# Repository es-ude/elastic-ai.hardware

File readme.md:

# Elastic Node Hardware Platform
This repo contains the hardware design files of our elastic node hardware for deploying deep learning architectures on embedded hardware.

## ENv6 - Elastic Node v6
Still in progress

## ENv5 - Elastic Node v5
The 5th generation of Elastic node is designed based on the 4th version, but with some improvements. The main improvements are:
- Using Cortex-M0 MCU instead of AVR 8-bit MCU, to gain more performance and lower power consumption.
- Using SPI as the communication interface between MCU and the FPGA to save more IO pins.
- Simplify the power supply circuit to reduce the space and improve reliability.
- Adding an energy meter chip to ease the energy measurement.
- Optimize the PCB layout to reduce the PCB size.

Before you start using the ENv5, please read the following documents accordingly:
- [ENv5 Test Version User Manual](v5/test_version/readme.md)
- [ENv5 Revision 1 User Manual](v5/revision_1/readme.md)

Troubleshooting
- When you notice the esp32 is not responding to the RP2040, you can apply the [pre-build firmware](v5/revision_1/prebuilds-firmware/test_esp_at.uf2) to test.
  - some descriptions about the behavior of the test are available [here](v5/revision_1/prebuilds-firmware/readme.md).

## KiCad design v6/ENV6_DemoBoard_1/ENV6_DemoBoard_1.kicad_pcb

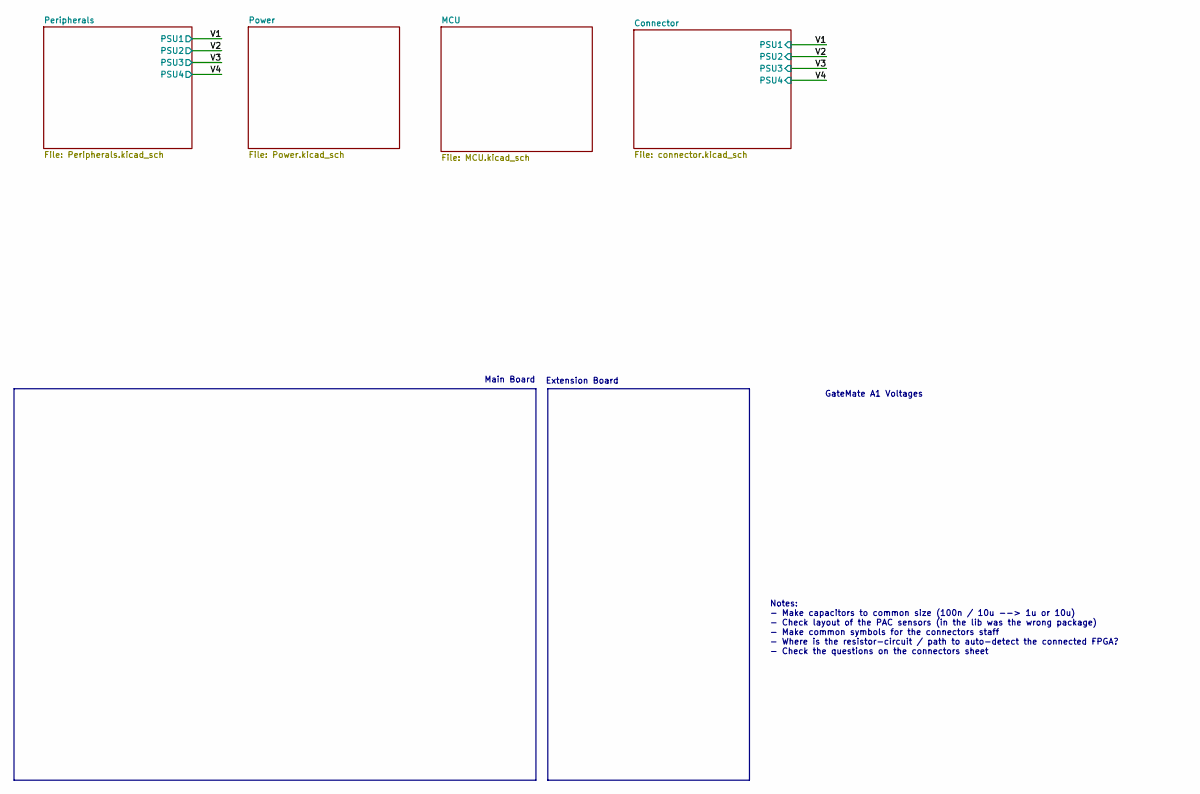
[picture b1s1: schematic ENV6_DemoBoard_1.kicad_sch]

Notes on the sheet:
Extension Board
Notes: - Make capacitors to common size (100n / 10u --> 1u or 10u) - Check layout of the PAC sensors (in the lib was the wrong package) - Make common symbols for the connectors staff - Where is the resistor-circuit / path to auto-detect the connected FPGA? - Check the questions on the connectors sh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
Main Board
GateMate A1 Voltages

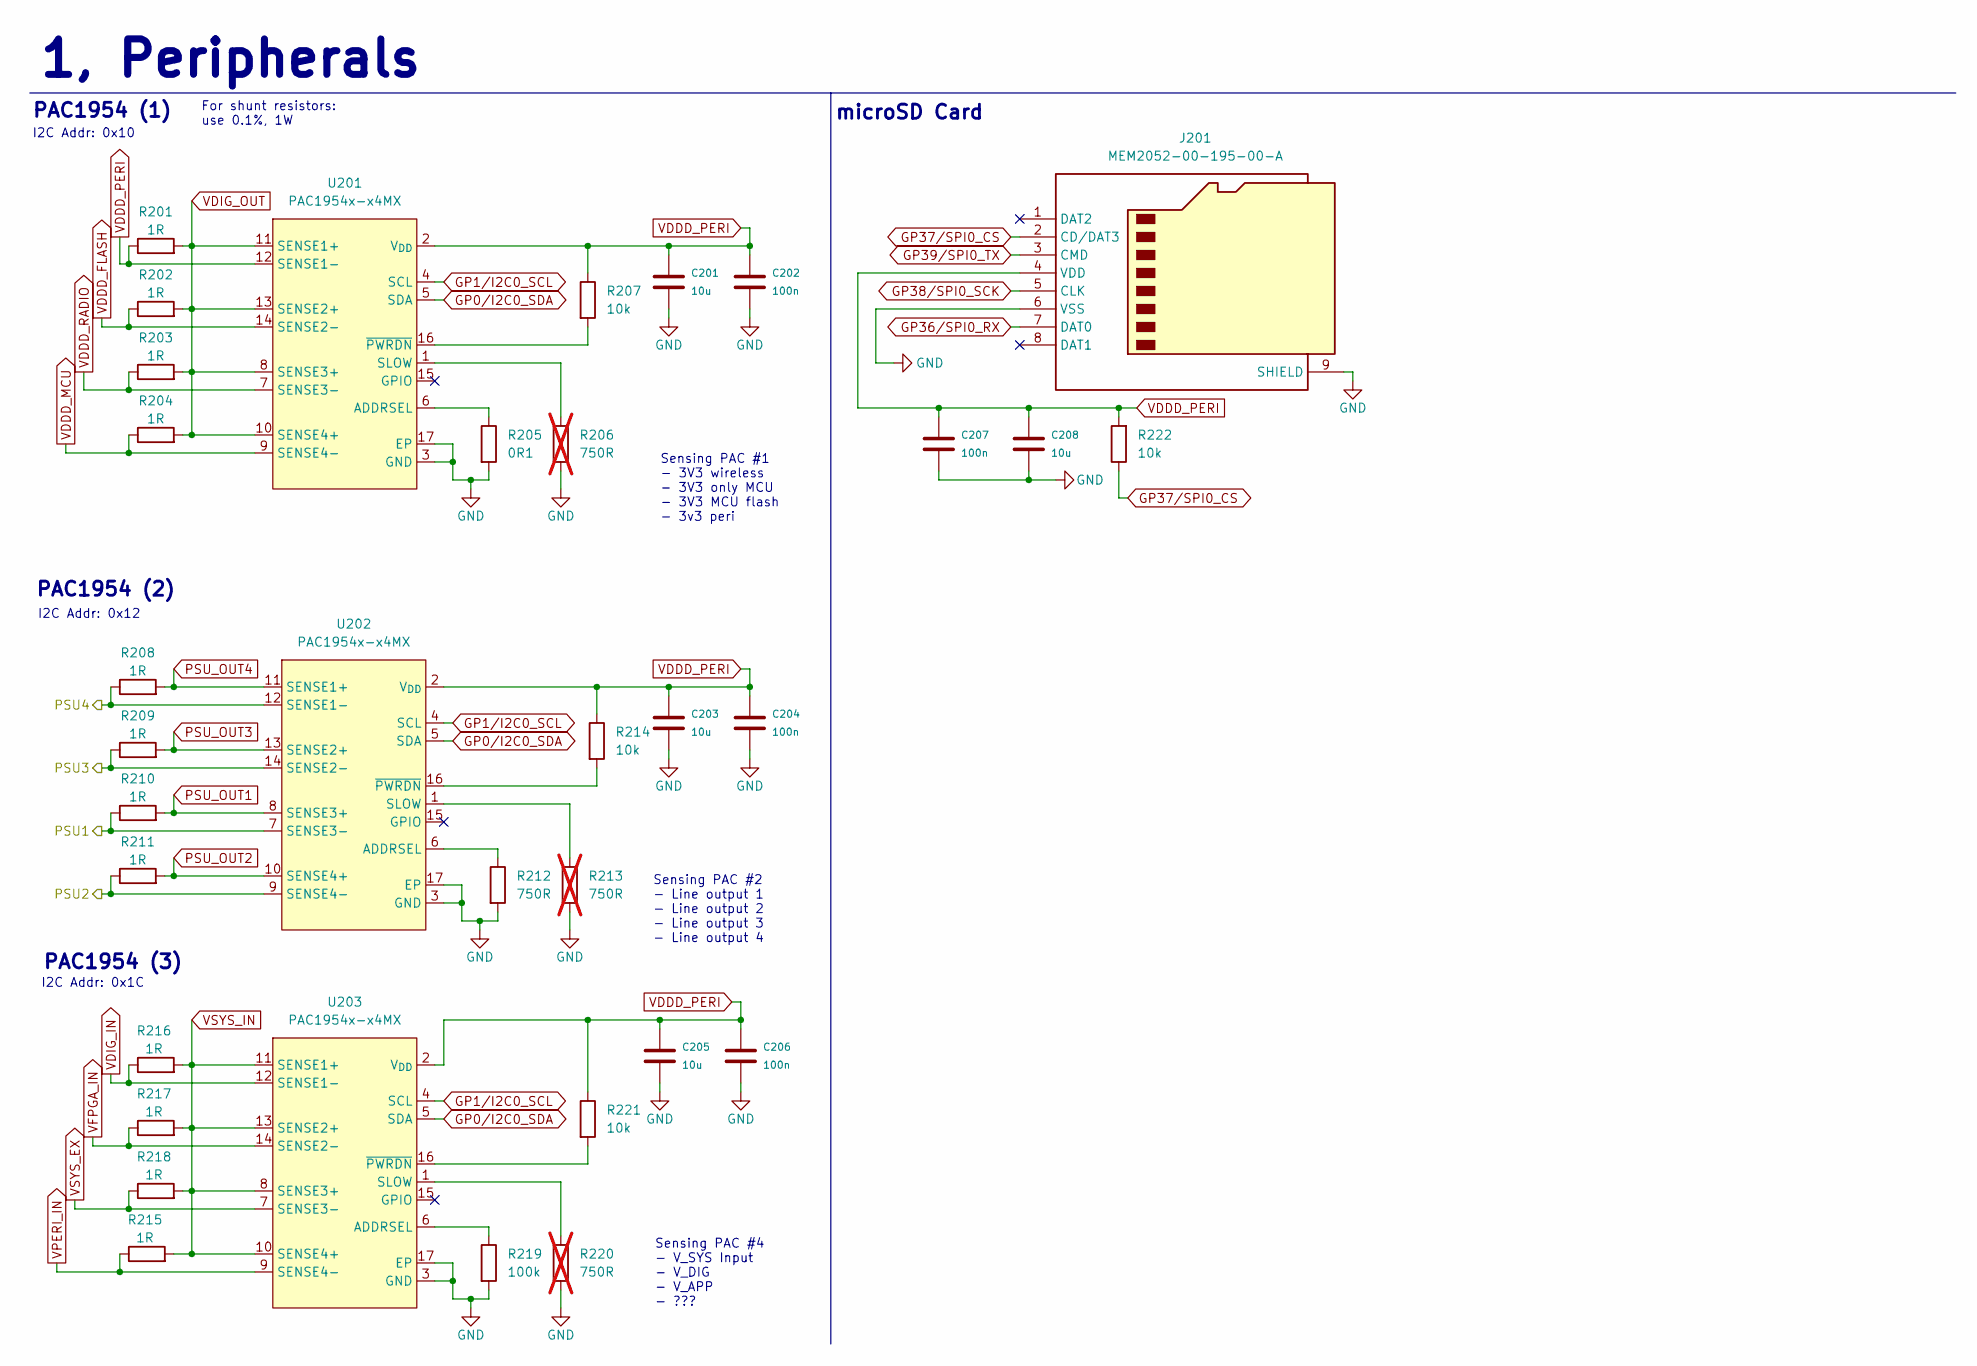
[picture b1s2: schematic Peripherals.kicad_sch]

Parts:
C201, C203, C205, C208: 10u; C_0402_1005Metric
C202, C204, C206, C207: 100n; C_0402_1005Metric
J201: MEM2052-00-195-00-A; MEM20520019500A; Mouser Part Number 640-MEM20520019500A
R201, R202, R203, R204, R208, R209, R210, R211, R215, R216, R217, R218: 1R; R_0603_1608Metric
R205: 0R1; R_0402_1005Metric
R206, R213, R220: 750R; R_0402_1005Metric; not fitted
R207, R214, R221, R222: 10k; R_0402_1005Metric
R212: 750R; R_0402_1005Metric
R219: 100k; R_0402_1005Metric
U201, U202, U203: PAC1954x-x4MX; VQFN-16-1EP_3x3mm_P0.5mm_EP1.1x1.1mm

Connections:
/V1: R210.1, U202.7 (SENSE3-); also elsewhere on the board
/V2: R211.1, U202.9 (SENSE4-); also elsewhere on the board
/V3: R209.1, U202.14 (SENSE2-); also elsewhere on the board
/V4: R208.1, U202.12 (SENSE1-); also elsewhere on the board
GND: C201.1, C202.1, C203.1, C204.1, C205.1, C206.1, C207.1, C208.1, J201.6 (VSS), J201.9 (SHIELD), J201.G1 (GND_1), J201.G2 (GND_2), J201.G3 (GND_3), J201.G4 (GND_4), R205.2, R206.2, R212.2, R213.2, R219.2, R220.2, U201.3 (GND), U201.17 (EP), U202.3 (GND), U202.17 (EP), U203.3 (GND), U203.17 (EP); also elsewhere on the board
GP0/I2C0_SDA: U201.5 (SDA), U202.5 (SDA), U203.5 (SDA); also elsewhere on the board
GP1/I2C0_SCL: U201.4 (SCL), U202.4 (SCL), U203.4 (SCL); also elsewhere on the board
GP36/SPI0_RX: J201.7 (DAT0); also elsewhere on the board
GP37/SPI0_CS: J201.2 (CD/DAT3), R222.1; also elsewhere on the board
GP38/SPI0_SCK: J201.5 (CLK); also elsewhere on the board
GP39/SPI0_TX: J201.3 (CMD); also elsewhere on the board
unnamed: R205.1, U201.6 (ADDRSEL)
unnamed: R206.1, U201.1 (SLOW)
unnamed: R207.2, U201.16 (~PWRDN)
unnamed: R212.1, U202.6 (ADDRSEL)
unnamed: R213.1, U202.1 (SLOW)
unnamed: R214.2, U202.16 (~PWRDN)
unnamed: R219.1, U203.6 (ADDRSEL)
unnamed: R220.1, U203.1 (SLOW)
unnamed: R221.2, U203.16 (~PWRDN)
PSU_OUT1: R210.2, U202.8 (SENSE3+); also elsewhere on the board
PSU_OUT2: R211.2, U202.10 (SENSE4+); also elsewhere on the board
PSU_OUT3: R209.2, U202.13 (SENSE2+); also elsewhere on the board
PSU_OUT4: R208.2, U202.11 (SENSE1+); also elsewhere on the board
VDDD_FLASH: R202.1, U201.14 (SENSE2-); also elsewhere on the board
VDDD_MCU: R204.1, U201.9 (SENSE4-); also elsewhere on the board
VDDD_PERI: C201.2, C202.2, C203.2, C204.2, C205.2, C206.2, C207.2, C208.2, J201.4 (VDD), R201.1, R207.1, R214.1, R221.1, R222.2, U201.2 (V_{DD}), U201.12 (SENSE1-), U202.2 (V_{DD}), U203.2 (V_{DD}); also elsewhere on the board
VDDD_RADIO: R203.1, U201.7 (SENSE3-); also elsewhere on the board
VDIG_IN: R216.1, U203.12 (SENSE1-); also elsewhere on the board
VDIG_OUT: R201.2, R202.2, R203.2, R204.2, U201.8 (SENSE3+), U201.10 (SENSE4+), U201.11 (SENSE1+), U201.13 (SENSE2+); also elsewhere on the board
VFPGA_IN: R217.1, U203.14 (SENSE2-); also elsewhere on the board
VPERI_IN: R215.1, U203.9 (SENSE4-); also elsewhere on the board
VSYS_EX: R218.1, U203.7 (SENSE3-); also elsewhere on the board
VSYS_IN: R215.2, R216.2, R217.2, R218.2, U203.8 (SENSE3+), U203.10 (SENSE4+), U203.11 (SENSE1+), U203.13 (SENSE2+); also elsewhere on the board

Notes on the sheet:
1, Peripherals
Sensing PAC #4 - V_SYS Input - V_DIG - V_APP - ???
PAC1954 (1)
microSD Card
Sensing PAC #1 - 3V3 wireless - 3V3 only MCU - 3V3 MCU flash - 3v3 peri
For shunt resistors: use 0.1%, 1W
I2C Addr: 0x1C
I2C Addr: 0x10
I2C Addr: 0x12
Sensing PAC #2 - Line output 1 - Line output 2 - Line output 3 - Line output 4
PAC1954 (2)
PAC1954 (3)

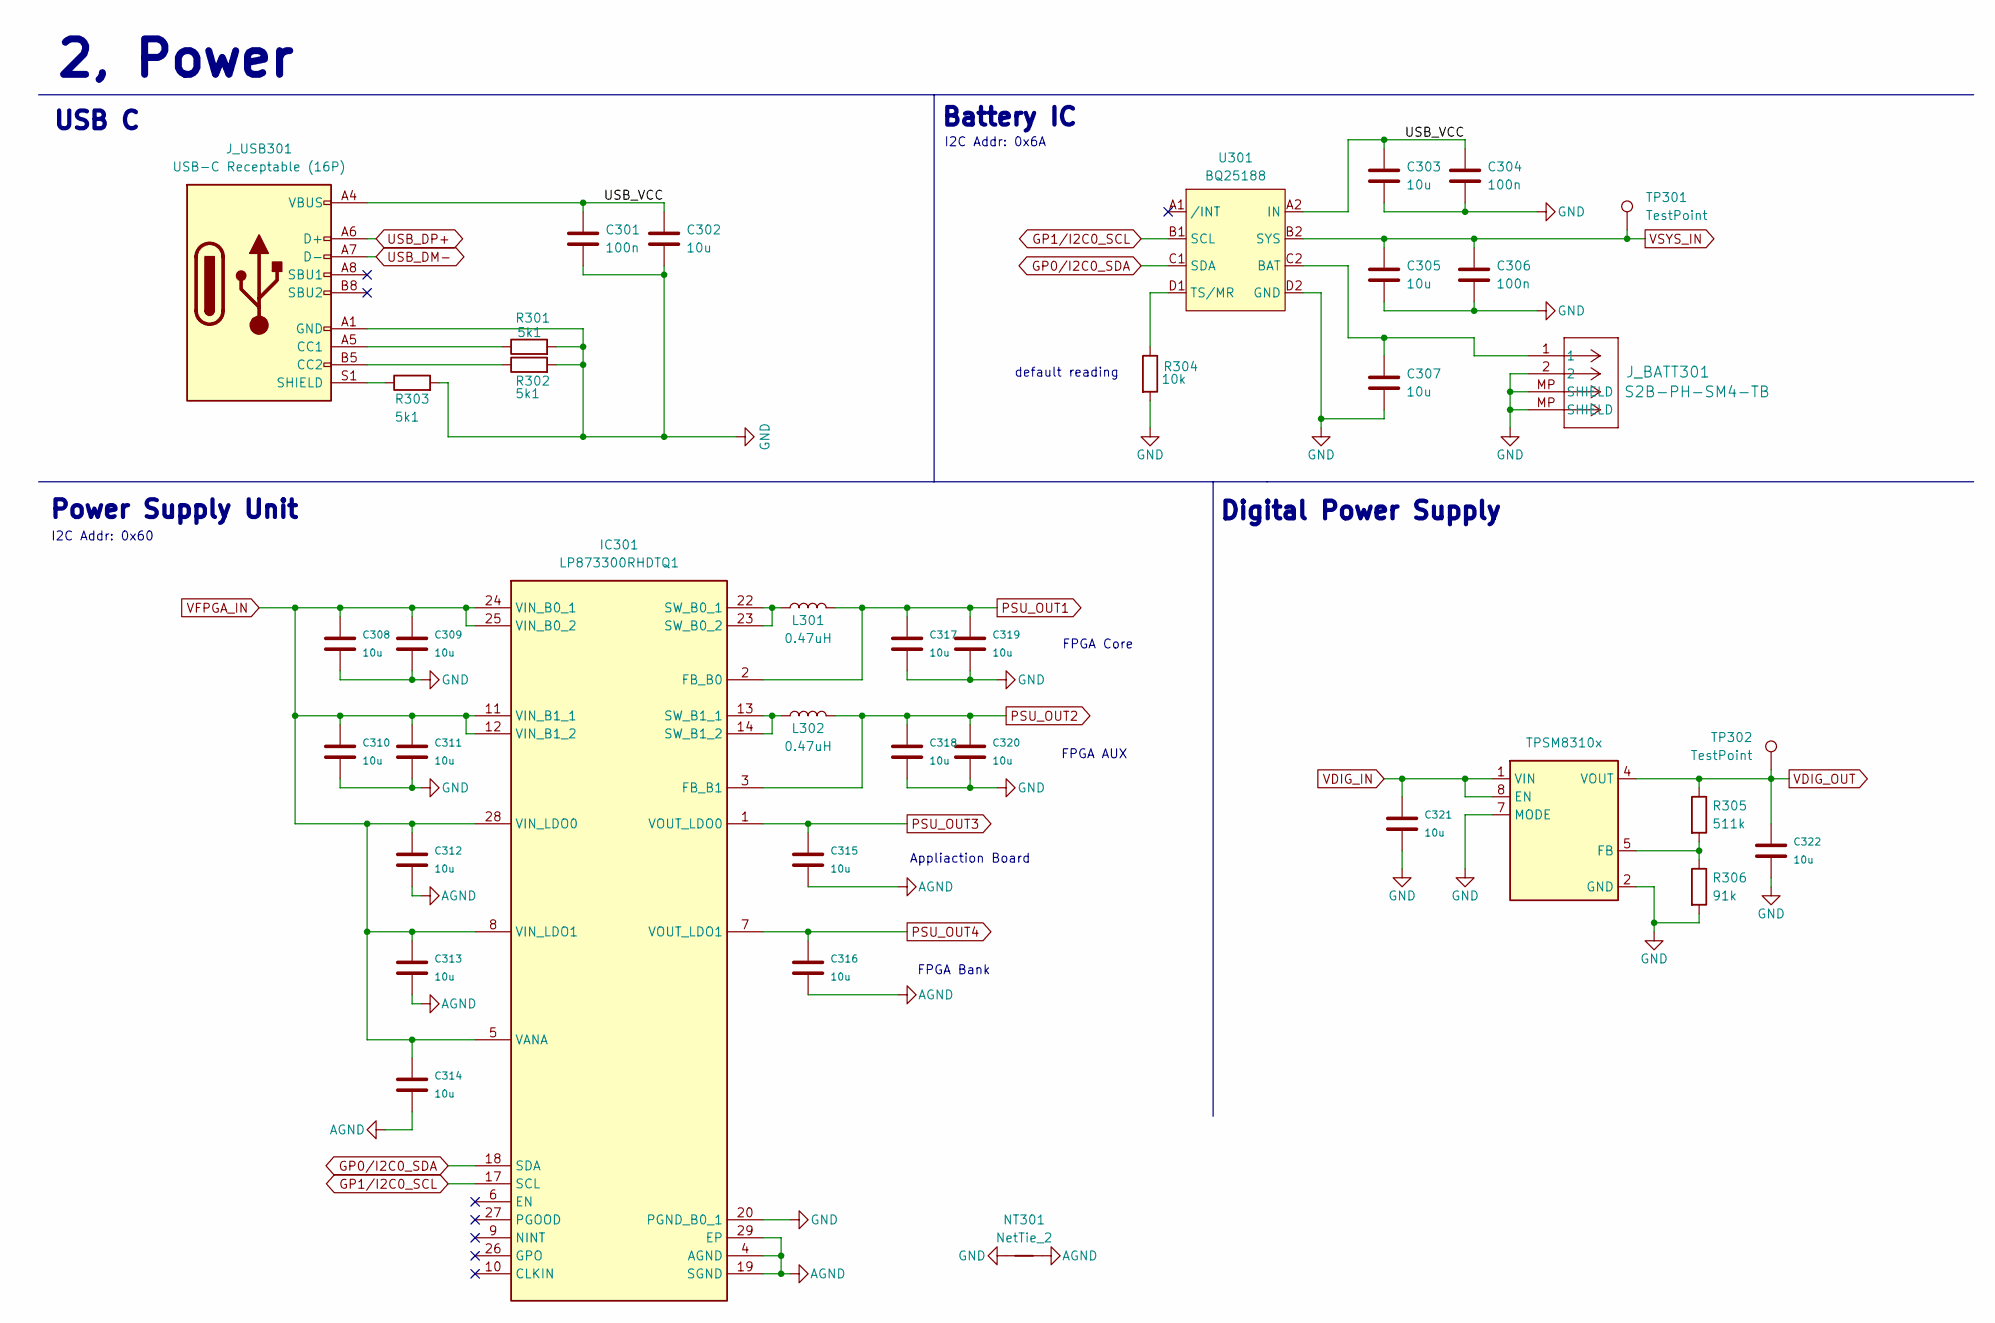
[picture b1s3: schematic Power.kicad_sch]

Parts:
C301, C304, C306: 100n; C_0402_1005Metric
C302, C303, C305, C307, C308, C309, C310, C311, C312, C313, C314, C315, C316, C317, C318, C319, C320, C321, C322: 10u; C_0402_1005Metric
IC301: LP873300RHDTQ1; QFN50P500X500X80-29N; Mouser Part Number 595-LP873300RHDTQ1
J_BATT301: S2B-PH-SM4-TB; JST_PH_S2B-PH-SM4-TB_1x02-1MP_P2.00mm_Horizontal
J_USB301: USB-C Receptable (16P); USB_C_Receptacle_16P
L301, L302: 0.47uH; L_1008_2520Metric
NT301: NetTie_2; NetTie-2_SMD_Pad0.5mm
R301, R302, R303: 5k1; R_0402_1005Metric
R304: 10k; R_0402_1005Metric
R305: 511k; R_0402_1005Metric
R306: 91k; R_0402_1005Metric
TP301, TP302: TestPoint; TestPoint_Pad_D1.0mm
U301: BQ25188; Texas_DSBGA-8_0.9x1.9mm_Layout2x4_P0.5mm
U302: TPSM8310x; MICROSIP8_SIU_TEX

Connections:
/Power/USB_VCC: C301.1, C302.1, C303.1, C304.1, J_USB301.A4 (VBUS), J_USB301.A9 (VBUS), J_USB301.B4 (VBUS), J_USB301.B9 (VBUS), U301.A2 (IN)
AGND: C312.1, C313.1, C314.1, C315.1, C316.1, IC301.4 (AGND), IC301.19 (SGND), IC301.29 (EP), NT301.2
GND: C301.2, C302.2, C303.2, C304.2, C305.2, C306.2, C307.2, C308.1, C309.1, C310.1, C311.1, C317.1, C318.1, C319.1, C320.1, C321.1, C322.1, IC301.15 (PGND_B1_1), IC301.16 (PGND_B1_2), IC301.20 (PGND_B0_1), IC301.21 (PGND_B0_2), J_BATT301.2, J_BATT301.MP (SHIELD), J_USB301.A1 (GND), J_USB301.A12 (GND), J_USB301.B1 (GND), J_USB301.B12 (GND), NT301.1, R301.2, R302.2, R303.2, R304.2, R306.2, U301.D2 (GND), U302.2 (GND), U302.3 (GND), U302.6 (GND), U302.7 (MODE); also elsewhere on the board
GP0/I2C0_SDA: IC301.18 (SDA), U301.C1 (SDA); also elsewhere on the board
GP1/I2C0_SCL: IC301.17 (SCL), U301.B1 (SCL); also elsewhere on the board
unnamed: IC301.22 (SW_B0_1), IC301.23 (SW_B0_2), L301.1
unnamed: IC301.13 (SW_B1_1), IC301.14 (SW_B1_2), L302.1
unnamed: J_USB301.A5 (CC1), R301.1
unnamed: J_USB301.B5 (CC2), R302.1
unnamed: J_USB301.S1 (SHIELD), R303.1
unnamed: C307.1, J_BATT301.1, U301.C2 (BAT)
unnamed: R304.1, U301.D1 (TS/MR)
unnamed: R305.2, R306.1, U302.5 (FB)
PSU_OUT1: C317.2, C319.2, IC301.2 (FB_B0), L301.2; also elsewhere on the board
PSU_OUT2: C318.2, C320.2, IC301.3 (FB_B1), L302.2; also elsewhere on the board
PSU_OUT3: C315.2, IC301.1 (VOUT_LDO0); also elsewhere on the board
PSU_OUT4: C316.2, IC301.7 (VOUT_LDO1); also elsewhere on the board
USB_DM-: J_USB301.A7 (D-), J_USB301.B7 (D-); also elsewhere on the board
USB_DP+: J_USB301.A6 (D+), J_USB301.B6 (D+); also elsewhere on the board
VDIG_IN: C321.2, U302.1 (VIN), U302.8 (EN); also elsewhere on the board
VDIG_OUT: C322.2, R305.1, TP302.1 (1_1), U302.4 (VOUT); also elsewhere on the board
VFPGA_IN: C308.2, C309.2, C310.2, C311.2, C312.2, C313.2, C314.2, IC301.5 (VANA), IC301.8 (VIN_LDO1), IC301.11 (VIN_B1_1), IC301.12 (VIN_B1_2), IC301.24 (VIN_B0_1), IC301.25 (VIN_B0_2), IC301.28 (VIN_LDO0); also elsewhere on the board
VSYS_IN: C305.1, C306.1, TP301.1 (1_1), U301.B2 (SYS); also elsewhere on the board

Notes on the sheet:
Battery IC
FPGA Bank
I2C Addr: 0x6A
default reading
USB C
2, Power
FPGA Core
Power Supply Unit
FPGA AUX
I2C Addr: 0x60
Digital Power Supply
Appliaction Board

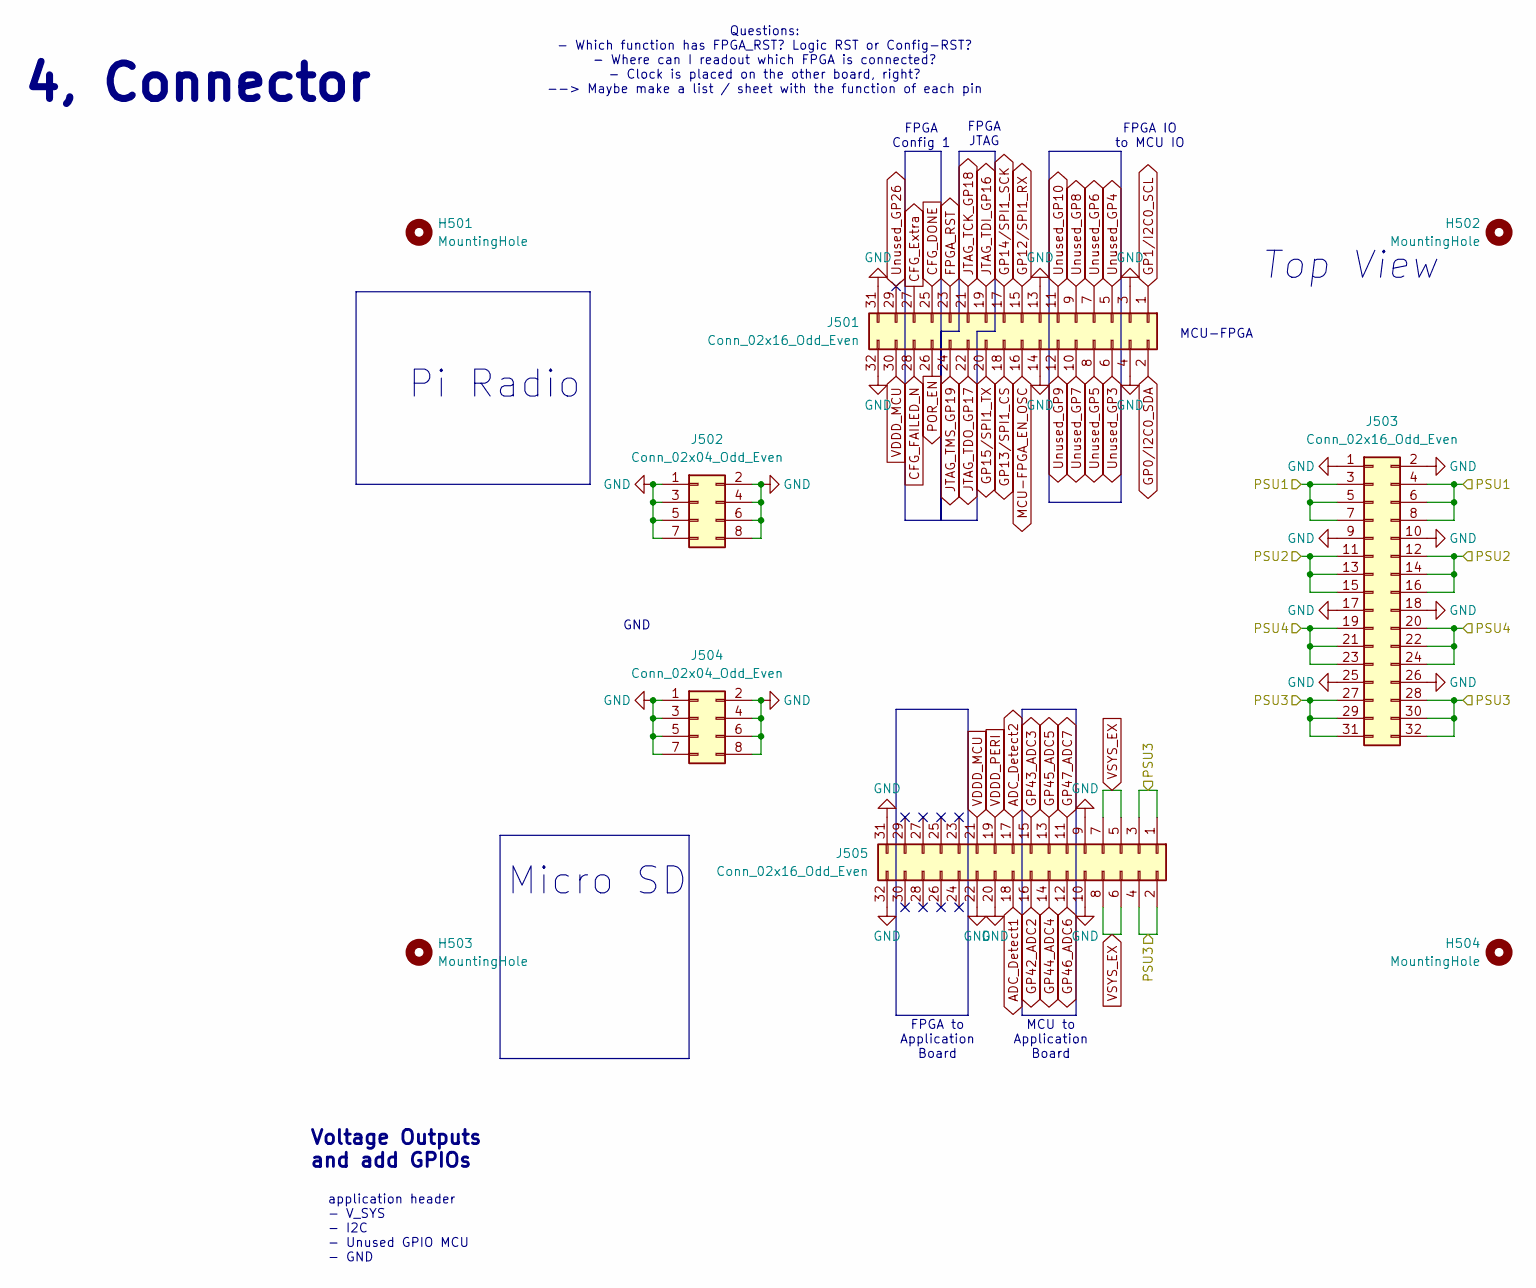
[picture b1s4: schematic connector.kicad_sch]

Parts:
H501, H502, H503, H504: MountingHole; MountingHole_2.5mm
J501, J503, J505: Conn_02x16_Odd_Even; PinHeader_2x16_P2.00mm_Vertical
J502, J504: Conn_02x04_Odd_Even; PinHeader_2x04_P2.00mm_Vertical

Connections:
/V1: J503.3, J503.4, J503.5, J503.6, J503.7, J503.8; also elsewhere on the board
/V2: J503.11, J503.12, J503.13, J503.14, J503.15, J503.16; also elsewhere on the board
/V3: J503.27, J503.28, J503.29, J503.30, J503.31, J503.32, J505.1, J505.2, J505.3, J505.4; also elsewhere on the board
/V4: J503.19, J503.20, J503.21, J503.22, J503.23, J503.24; also elsewhere on the board
ADC_Detect1: J505.18; also elsewhere on the board
ADC_Detect2: J505.17; also elsewhere on the board
CFG_DONE: J501.25; also elsewhere on the board
CFG_Extra: J501.27; also elsewhere on the board
CFG_FAILED_N: J501.28; also elsewhere on the board
FPGA_RST: J501.23; also elsewhere on the board
GND: J501.3, J501.4, J501.13, J501.14, J501.31, J501.32, J502.1, J502.2, J502.3, J502.4, J502.5, J502.6, J502.7, J502.8, J503.1, J503.2, J503.9, J503.10, J503.17, J503.18, J503.25, J503.26, J504.1, J504.2, J504.3, J504.4, J504.5, J504.6, J504.7, J504.8, J505.9, J505.10, J505.20, J505.22, J505.31, J505.32; also elsewhere on the board
GP0/I2C0_SDA: J501.2; also elsewhere on the board
GP1/I2C0_SCL: J501.1; also elsewhere on the board
GP12/SPI1_RX: J501.15; also elsewhere on the board
GP13/SPI1_CS: J501.18; also elsewhere on the board
GP14/SPI1_SCK: J501.17; also elsewhere on the board
GP15/SPI1_TX: J501.20; also elsewhere on the board
GP42_ADC2: J505.16; also elsewhere on the board
GP43_ADC3: J505.15; also elsewhere on the board
GP44_ADC4: J505.14; also elsewhere on the board
GP45_ADC5: J505.13; also elsewhere on the board
GP46_ADC6: J505.12; also elsewhere on the board
GP47_ADC7: J505.11; also elsewhere on the board
JTAG_TCK_GP18: J501.21; also elsewhere on the board
JTAG_TDI_GP16: J501.19; also elsewhere on the board
JTAG_TDO_GP17: J501.22; also elsewhere on the board
JTAG_TMS_GP19: J501.24; also elsewhere on the board
MCU-FPGA_EN_OSC: J501.16; also elsewhere on the board
POR_EN: J501.26; also elsewhere on the board
Unused_GP3: J501.6; also elsewhere on the board
Unused_GP4: J501.5; also elsewhere on the board
Unused_GP5: J501.8; also elsewhere on the board
Unused_GP6: J501.7; also elsewhere on the board
Unused_GP7: J501.10; also elsewhere on the board
Unused_GP8: J501.9; also elsewhere on the board
Unused_GP9: J501.12; also elsewhere on the board
Unused_GP10: J501.11; also elsewhere on the board
Unused_GP26: J501.29; also elsewhere on the board
VDDD_MCU: J501.30, J505.21; also elsewhere on the board
VDDD_PERI: J505.19; also elsewhere on the board
VSYS_EX: J505.5, J505.6, J505.7, J505.8; also elsewhere on the board

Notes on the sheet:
MCU-FPGA
FPGA IO to MCU IO
Questions: - Which function has FPGA_RST? Logic RST or Config-RST? - Where can I readout which FPGA is connected? - Clock is placed on the other board, right? --> Maybe make a list / sheet with the function of each pin
FPGA to Application Board
Top View
MCU to Application Board
4, Connector
GND
FPGA JTAG
Micro SD
Pi Radio
application header - V_SYS - I2C - Unused GPIO MCU - GND
Voltage Outputs and add GPIOs
FPGA Config 1

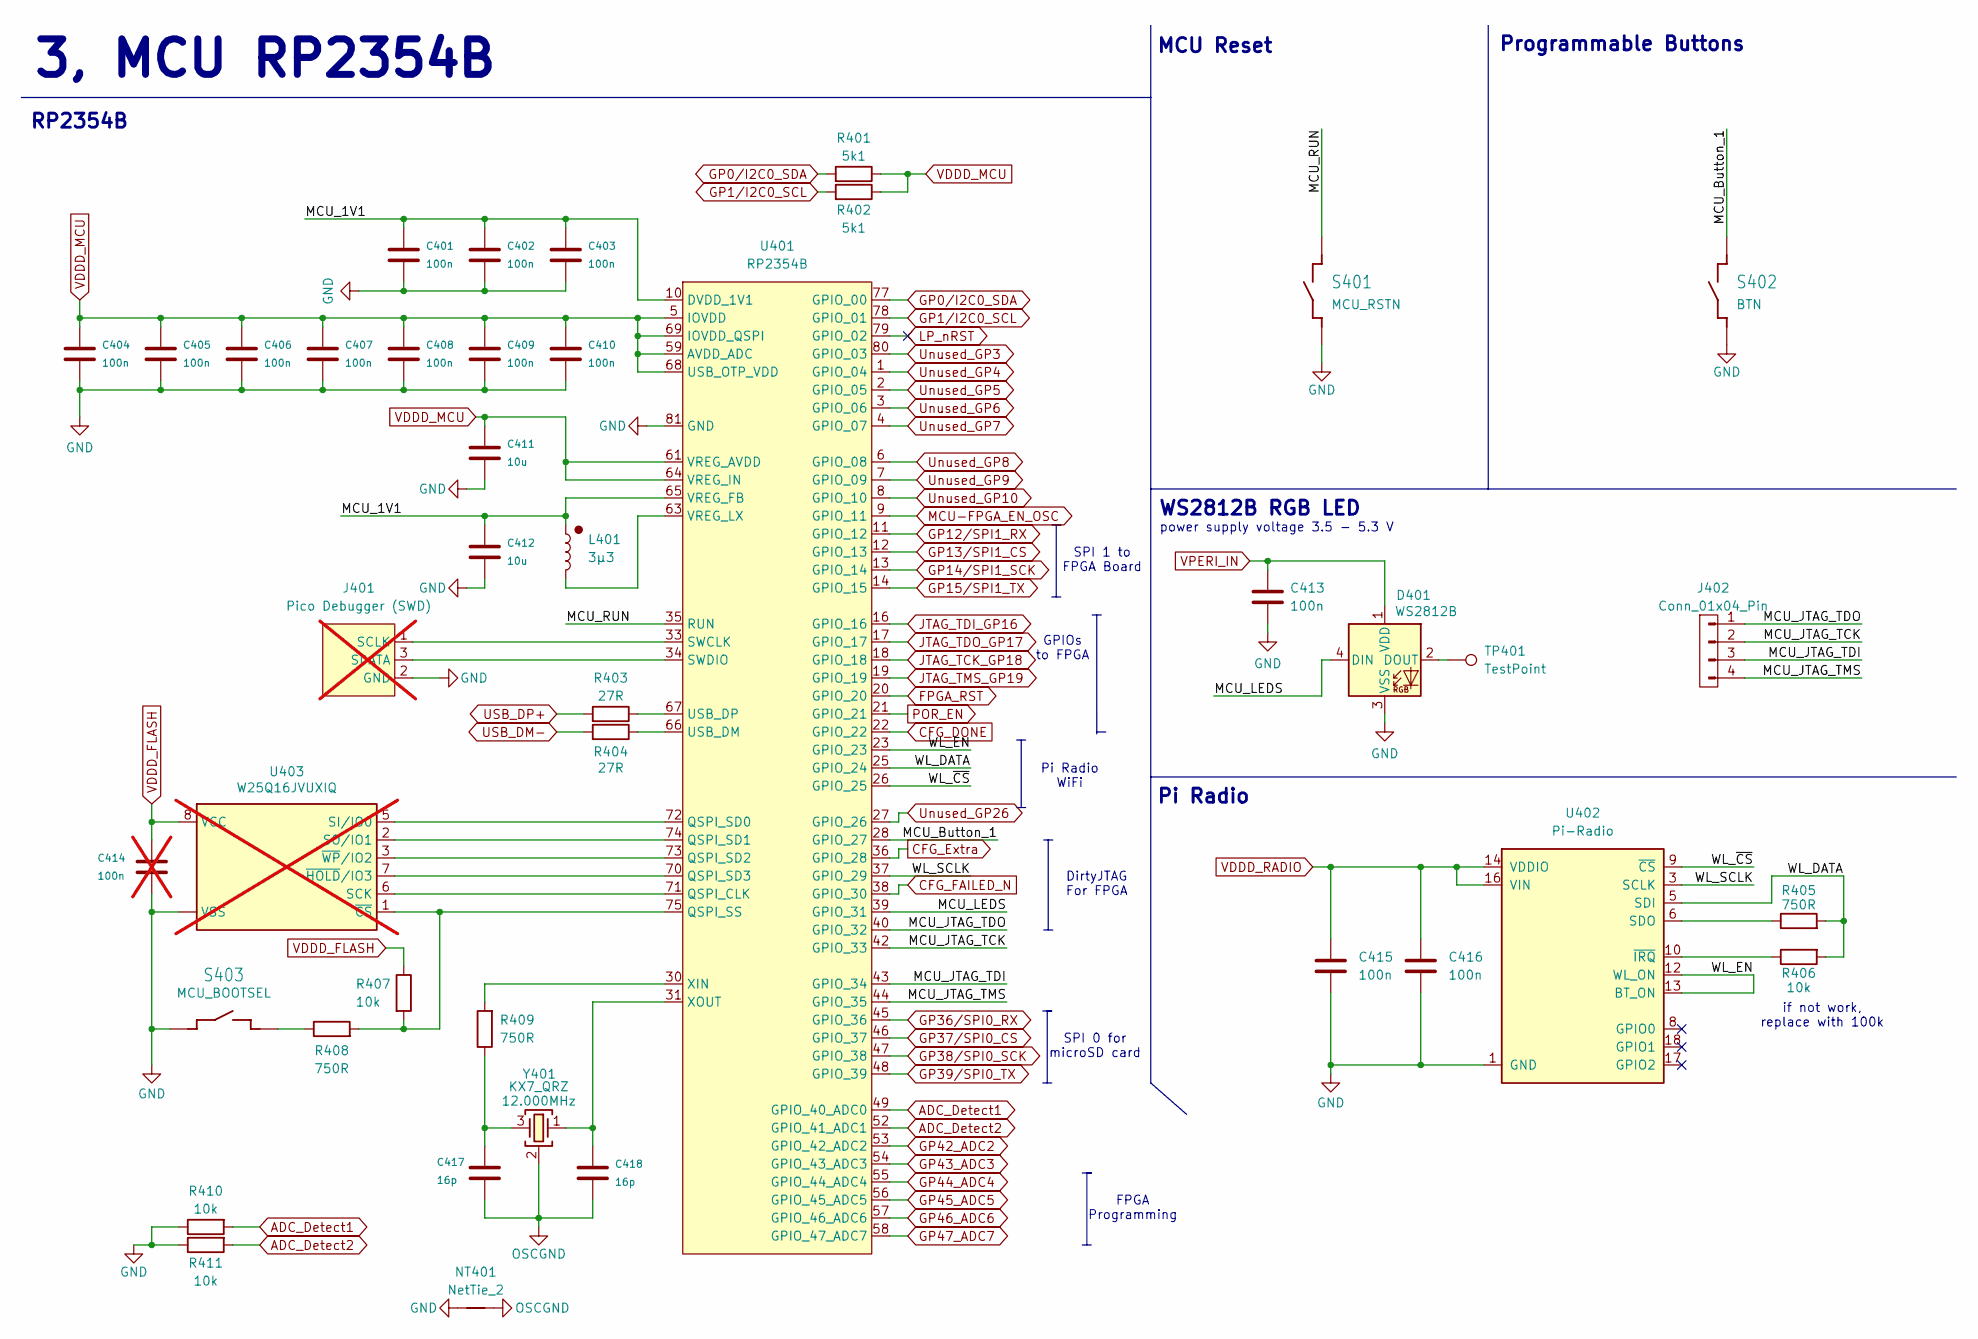
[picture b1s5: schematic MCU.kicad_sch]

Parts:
C401, C402, C403, C404, C405, C406, C407, C408, C409, C410, C413, C415, C416: 100n; C_0402_1005Metric
C411, C412: 10u; C_0402_1005Metric
C414: 100n; C_0402_1005Metric; not fitted
C417, C418: 16p; C_0402_1005Metric
D401: WS2812B; LED_WS2812B_PLCC4_5.0x5.0mm_P3.2mm
J401: Pico Debugger (SWD); PinHeader_1x03_P2.00mm_Vertical; not fitted
J402: Conn_01x04_Pin; PinSocket_1x04_P2.00mm_Vertical
L401: 3µ3; L_0805_2012_metric_Alligned_HandSolder
NT401: NetTie_2; NetTie-2_SMD_Pad0.5mm
R401, R402: 5k1; R_0402_1005Metric
R403, R404: 27R; R_0402_1005Metric
R405, R408, R409: 750R; R_0402_1005Metric
R406, R407, R410, R411: 10k; R_0402_1005Metric
S401: MCU_RSTN; TACTILE-SWITCH
S402: BTN; TACTILE-SWITCH
S403: MCU_BOOTSEL; TACTILE-SWITCH
TP401: TestPoint; TestPoint_Pad_D1.0mm
U401: RP2354B; QFN-80_EP_10x10_Pitch0.4mm
U402: Pi-Radio; RPi-Radio-Module
U403: W25Q16JVUXIQ; USON-8-1EP_3x2mm_P0.5mm_EP0.2x1.6mm; not fitted
Y401: KX7_QRZ; KX-7; MPN ABM8G-25.000MHZ-18-D2Y-T3

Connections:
/MCU/MCU_1V1: C401.2, C402.2, C403.2, C412.2, L401.1, U401.10 (DVDD_1V1), U401.32 (DVDD_1V1), U401.51 (DVDD_1V1), U401.65 (VREG_FB)
/MCU/MCU_Button_1: S402.3 (2), S402.4 (2), U401.28 (GPIO_27)
/MCU/MCU_JTAG_TCK: J402.2, U401.42 (GPIO_33)
/MCU/MCU_JTAG_TDI: J402.3, U401.43 (GPIO_34)
/MCU/MCU_JTAG_TDO: J402.1, U401.40 (GPIO_32)
/MCU/MCU_JTAG_TMS: J402.4, U401.44 (GPIO_35)
/MCU/MCU_LEDS: D401.4 (DIN), U401.39 (GPIO_31)
/MCU/MCU_RUN: S401.3 (2), S401.4 (2), U401.35 (RUN)
/MCU/WL_DATA: R405.2, R406.2, U401.25 (GPIO_24), U402.5 (SDI)
/MCU/WL_EN: U401.23 (GPIO_23), U402.12 (WL_ON), U402.13 (BT_ON)
/MCU/WL_SCLK: U401.37 (GPIO_29), U402.3 (SCLK)
/MCU/WL_~CS: U401.26 (GPIO_25), U402.9 (~CS)
ADC_Detect1: R410.2, U401.49 (GPIO_40_ADC0); also elsewhere on the board
ADC_Detect2: R411.2, U401.52 (GPIO_41_ADC1); also elsewhere on the board
CFG_DONE: U401.22 (GPIO_22); also elsewhere on the board
CFG_Extra: U401.36 (GPIO_28); also elsewhere on the board
CFG_FAILED_N: U401.38 (GPIO_30); also elsewhere on the board
FPGA_RST: U401.20 (GPIO_20); also elsewhere on the board
GND: C401.1, C402.1, C403.1, C404.1, C405.1, C406.1, C407.1, C408.1, C409.1, C410.1, C411.1, C412.1, C413.2, C414.2, C415.2, C416.2, D401.3 (VSS), J401.2 (GND), NT401.1, R410.1, R411.1, S401.1, S401.2 (1), S402.1, S402.2 (1), S403.1, S403.2 (1), U401.62 (GND), U401.81 (GND), U402.1 (GND), U402.4 (GND), U402.7 (GND), U402.11 (GND), U402.15 (GND), U402.21 (GND), U403.4 (VSS), U403.9 (VSS); also elsewhere on the board
GP0/I2C0_SDA: R401.2, U401.77 (GPIO_00); also elsewhere on the board
GP1/I2C0_SCL: R402.2, U401.78 (GPIO_01); also elsewhere on the board
GP12/SPI1_RX: U401.11 (GPIO_12); also elsewhere on the board
GP13/SPI1_CS: U401.12 (GPIO_13); also elsewhere on the board
GP14/SPI1_SCK: U401.13 (GPIO_14); also elsewhere on the board
GP15/SPI1_TX: U401.14 (GPIO_15); also elsewhere on the board
GP36/SPI0_RX: U401.45 (GPIO_36); also elsewhere on the board
GP37/SPI0_CS: U401.46 (GPIO_37); also elsewhere on the board
GP38/SPI0_SCK: U401.47 (GPIO_38); also elsewhere on the board
GP39/SPI0_TX: U401.48 (GPIO_39); also elsewhere on the board
GP42_ADC2: U401.53 (GPIO_42_ADC2); also elsewhere on the board
GP43_ADC3: U401.54 (GPIO_43_ADC3); also elsewhere on the board
GP44_ADC4: U401.55 (GPIO_44_ADC4); also elsewhere on the board
GP45_ADC5: U401.56 (GPIO_45_ADC5); also elsewhere on the board
GP46_ADC6: U401.57 (GPIO_46_ADC6); also elsewhere on the board
GP47_ADC7: U401.58 (GPIO_47_ADC7); also elsewhere on the board
JTAG_TCK_GP18: U401.18 (GPIO_18); also elsewhere on the board
JTAG_TDI_GP16: U401.16 (GPIO_16); also elsewhere on the board
JTAG_TDO_GP17: U401.17 (GPIO_17); also elsewhere on the board
JTAG_TMS_GP19: U401.19 (GPIO_19); also elsewhere on the board
LP_nRST: U401.79 (GPIO_02)
MCU-FPGA_EN_OSC: U401.9 (GPIO_11); also elsewhere on the board
unnamed: C417.2, R409.1, Y401.3
unnamed: D401.2 (DOUT), TP401.1 (1_1)
unnamed: J401.1 (SCLK), U401.33 (SWCLK)
unnamed: J401.3 (SDATA), U401.34 (SWDIO)
unnamed: R408.1, S403.3 (2), S403.4 (2)
unnamed: U401.71 (QSPI_CLK), U403.6 (SCK)
unnamed: U401.72 (QSPI_SD0), U403.5 (SI/IO0)
unnamed: U401.74 (QSPI_SD1), U403.2 (SO/IO1)
unnamed: U401.73 (QSPI_SD2), U403.3 (~WP/IO2)
unnamed: U401.70 (QSPI_SD3), U403.7 (~HOLD/IO3)
unnamed: R407.2, R408.2, U401.75 (QSPI_SS), U403.1 (~CS)
unnamed: R404.1, U401.66 (USB_DM)
unnamed: R403.1, U401.67 (USB_DP)
unnamed: L401.2, U401.63 (VREG_LX)
unnamed: R409.2, U401.30 (XIN)
unnamed: C418.2, U401.31 (XOUT), Y401.1
unnamed: R405.1, U402.6 (SDO)
unnamed: R406.1, U402.10 (~IRQ)
OSCGND: C417.1, C418.1, NT401.2, Y401.2 (SH), Y401.4 (SH)
POR_EN: U401.21 (GPIO_21); also elsewhere on the board
USB_DM-: R404.2; also elsewhere on the board
USB_DP+: R403.2; also elsewhere on the board
Unused_GP3: U401.80 (GPIO_03); also elsewhere on the board
Unused_GP4: U401.1 (GPIO_04); also elsewhere on the board
Unused_GP5: U401.2 (GPIO_05); also elsewhere on the board
Unused_GP6: U401.3 (GPIO_06); also elsewhere on the board
Unused_GP7: U401.4 (GPIO_07); also elsewhere on the board
Unused_GP8: U401.6 (GPIO_08); also elsewhere on the board
Unused_GP9: U401.7 (GPIO_09); also elsewhere on the board
Unused_GP10: U401.8 (GPIO_10); also elsewhere on the board
Unused_GP26: U401.27 (GPIO_26); also elsewhere on the board
VDDD_FLASH: C414.1, R407.1, U403.8 (VCC); also elsewhere on the board
VDDD_MCU: C404.2, C405.2, C406.2, C407.2, C408.2, C409.2, C410.2, C411.2, R401.1, R402.1, U401.5 (IOVDD), U401.15 (IOVDD), U401.24 (IOVDD), U401.29 (IOVDD), U401.41 (IOVDD), U401.50 (IOVDD), U401.59 (AVDD_ADC), U401.60 (IOVDD), U401.61 (VREG_AVDD), U401.64 (VREG_IN), U401.68 (USB_OTP_VDD), U401.69 (IOVDD_QSPI), U401.76 (IOVDD); also elsewhere on the board
VDDD_RADIO: C415.1, C416.1, U402.14 (VDDIO), U402.16 (VIN); also elsewhere on the board
VPERI_IN: C413.1, D401.1 (VDD); also elsewhere on the board

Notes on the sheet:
SPI 0 for microSD card
FPGA Programming
Programmable Buttons
GPIOs to FPGA
Pi Radio WiFi
Pi Radio
if not work, replace with 100k
RP2354B
SPI 1 to FPGA Board
3, MCU RP2354B
DirtyJTAG For FPGA
power supply voltage 3.5 - 5.3 V
WS2812B RGB LED
MCU Reset

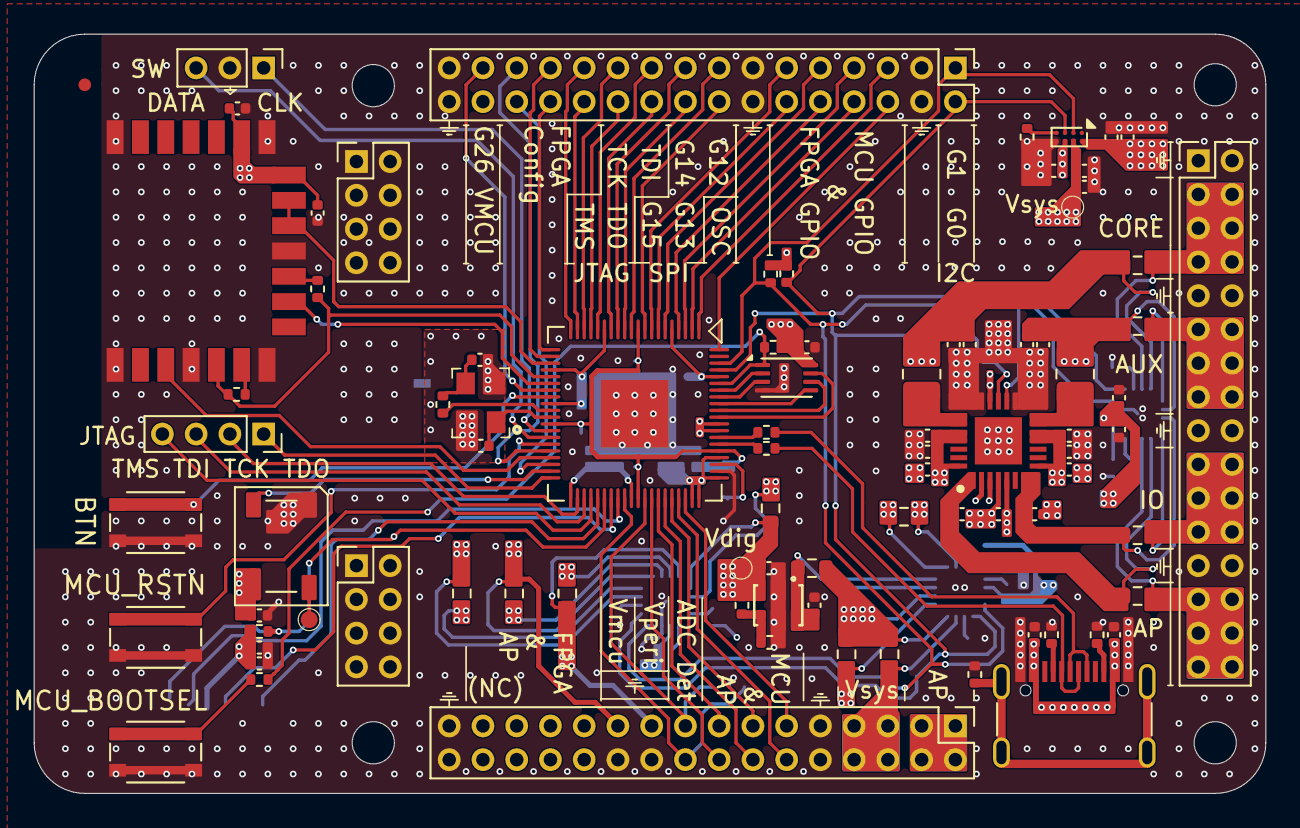
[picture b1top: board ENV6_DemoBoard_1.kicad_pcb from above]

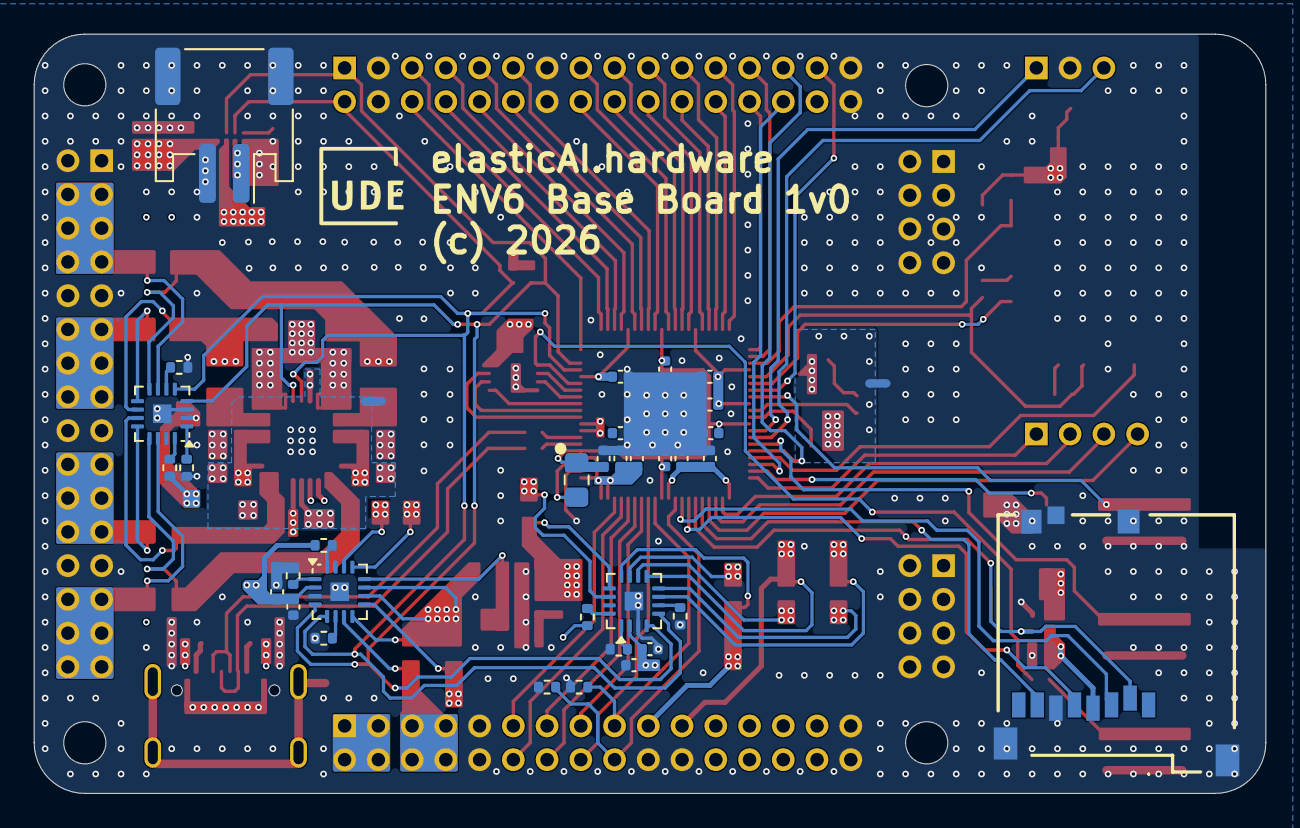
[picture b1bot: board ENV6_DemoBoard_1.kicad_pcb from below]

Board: 4 copper layers, 73.0 x 45.0 mm, 123 parts (35 on the bottom side), 108 nets.

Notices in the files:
measurement/mxo_offset_full/MXO_Offset_Generator.kicad_pcb:
UDE-ES (c) 2024
v6/ENV6_DemoBoard_1/ENV6_DemoBoard_1.kicad_pcb:
(c) 2026
parts and their libraries:
License: Apache-2.0
